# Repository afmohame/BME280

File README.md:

# BME280
Display temperature or humidity on 7 segment displays and with serial commincation (pressure with seria communication)

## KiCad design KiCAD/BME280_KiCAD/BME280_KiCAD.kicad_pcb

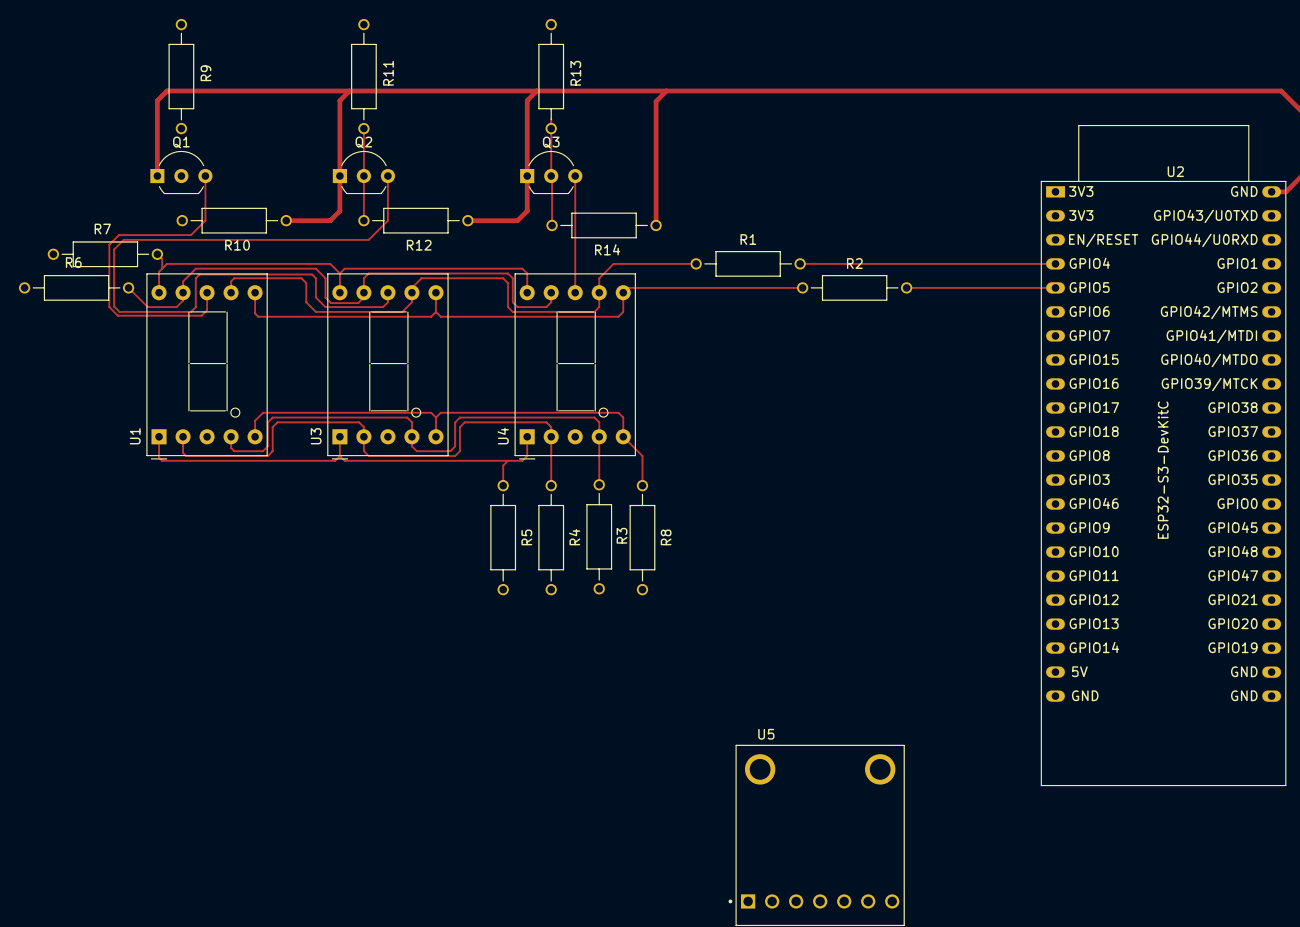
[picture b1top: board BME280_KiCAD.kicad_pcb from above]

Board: 2 copper layers, 22 parts (0 on the bottom side), 29 nets.

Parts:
Q1, Q2, Q3: 2N7000; TO-92_Inline_Wide
R1, R2, R3, R4, R5, R6, R7, R8: 300; RESAD1100W55L680D260
R9, R11, R13: 100; RESAD1100W55L680D260
R10, R12, R14: 20k; RESAD1100W55L680D260
U1, U3, U4: D148K; D1X8K
U2: ESP32-S3-DevKitC; ESP32-S3
U5: 2652; MODULE_2652

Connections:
GND: Q1.1 (S), Q2.1 (S), Q3.1 (S), R10.1, R12.1, R14.1, U2.22 (GND), U2.23 (GND), U2.24 (GND), U2.44 (GND), U5.3 (GND)
GPIO 2: R9.1, U2.40 (GPIO2/ADC1_CH1)
GPIO 4: R1.1, U2.4 (GPIO4/ADC1_CH3)
GPIO 5: R2.1, U2.5 (GPIO5/ADC1_CH4)
GPIO 6: R3.1, U2.6 (GPIO6/ADC1_CH5)
GPIO 7: R4.1, U2.7 (GPIO7/ADC1_CH6)
GPIO 10: R5.1, U2.10 (GPIO17/ADC2_CH6)
GPIO 11: R6.1, U2.11 (GPIO18/ADC2_CH7)
GPIO 12: R7.1, U2.12 (GPIO8/ADC1_CH7)
GPIO 13: R8.1, U2.13 (GPIO3/ADC1_CH2)
GPIO 41: R11.1, U2.38 (GPIO41/MTDI)
GPIO 42: R13.1, U2.39 (GPIO42/MTMS)
unnamed: Q1.3 (D), U1.8 (CC)
unnamed: Q1.2 (G), R9.2, R10.2
unnamed: Q2.3 (D), U3.8 (CC)
unnamed: Q2.2 (G), R11.2, R12.2
unnamed: Q3.3 (D), U4.8 (CC)
unnamed: Q3.2 (G), R13.2, R14.2
unnamed: R1.2, U1.7 (A), U3.7 (A), U4.7 (A)
unnamed: R2.2, U1.6 (B), U3.6 (B), U4.6 (B)
unnamed: R3.2, U1.4 (C), U3.4 (C), U4.4 (C)
unnamed: R4.2, U1.2 (D), U3.2 (D), U4.2 (D)
unnamed: R8.2, U1.5 (DP), U3.5 (DP), U4.5 (DP)
unnamed: R5.2, U1.1 (E), U3.1 (E), U4.1 (E)
unnamed: R6.2, U1.9 (F), U3.9 (F), U4.9 (F)
unnamed: R7.2, U1.10 (G), U3.10 (G), U4.10 (G)
SCL: U2.8 (GPIO15/ADC2_CH4/32K_P), U5.4 (SCK/SCL)
SDA: U2.9 (GPIO16/ADC2_CH5/32K_N), U5.6 (SDI/SDA)
VCC (3.3V): U2.1 (3V3), U2.2 (3V3), U5.2 (3VO), U5.5 (SDO)

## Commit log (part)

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2025-11-06 made the schematic and pcb, but BME280 not added at this moment
2026-02-06 added code folder with a template file and the file where the full code will be.
2026-02-16 controlled one 7-segment display by using arrays and not switch and cases. Issue with esp32 letting pin 42 HIGH research needed.
